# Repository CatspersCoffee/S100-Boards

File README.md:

# S100-Boards

S-100 bus boards designed, laid out and built for a home-built S-100 system between 2013 and 2016: Z80 and 80386 CPU cards, static and dynamic memory, I/O and SPI peripheral cards, an 18-slot backplane and bus termination. The designs are in KiCad, with Xilinx CPLD and FPGA logic on most boards.

## Background

The S-100 bus began with the MITS Altair 8800 in 1975 and was standardised as IEEE-696 in 1983. Hobbyists still design new boards for it today. John Monahan's S100Computers.com and the N8VEM project are two well-known sources, and several boards here started from their designs.

This work ran from 2013 to 2016:
- **2013:** a Z80 single-board computer and the 18-slot backplane.
- **2014:** the Z80 CPU card, the 8MB SRAM boards, the serial-flash development board and the Spartan-6 I/O card.
- **2015:** the CPLD versions of the Z80 card, the 80386 CPU card, the SPI I/O board and the 32-bit memory experiments.
- **2016:** a revised backplane and the 8259A/SPI board.

The original S-100 cards of the 1970s and 80s were built from dozens of TTL chips, and later from HCMOS. A thread running through these boards is to move that glue logic into Xilinx CPLDs (XC9572, XC9572XL, XC95288XL) and Spartan-6 FPGAs. This covers bus status decoding, board select and address compare, memory bank and chip-select decoding, and I/O port decoding.
- **8MB SRAM board:** Rev 1 uses 27 TTL logic chips. Rev 2 does the same job with 14, one of them an XC9572XL.
- **Z80 CPU card:** from REV 4.0 an XC9572 takes over the S-100 status and control logic.
- **Other boards:** the CPLD or FPGA implements I/O ports and SPI interfaces that would otherwise need extra discrete logic.

## Boards

| Board | Folder | What it is | Status |
|---|---|---|---|
| Z80 CPU | [`Z80-CPU/`](Z80-CPU/) | Z80 bus-master CPU card, four revisions (REV 1.0–5.0); XC9572 CPLD from REV 4.0 | Built (all revisions) |
| 80386 CPU (V3.1) | [`80386-CPU/`](80386-CPU/) | John Monahan's S100Computers 80386 CPU board with small changes | Built |
| 18-slot backplane | [`Backplane-18-Slot/`](Backplane-18-Slot/) | 18-slot motherboard with active termination, Rev 1.0 and Rev 2.0 | Built (both) |
| Serial Flash board | [`Flash-UART/`](Flash-UART/) | USB UART, TMA lines and four SPI flash chips loaded over USB (CH341A); XC95288XL CPLD | Built |
| S6LX9 FPGA & I/O | [`S6LX9-FPGA-IO/`](S6LX9-FPGA-IO/) | Spartan-6 XC6SLX9 I/O card with RTC and serial RAM/flash | Built |
| MCP Serial Peripheral I/O | [`XC9500-IO/`](XC9500-IO/) | XC9572 CPLD + 12× MCP23S08 SPI port expanders (96 I/O lines) | Built |
| PIC-SPI | [`PIC-SPI/`](PIC-SPI/) | 8259A interrupt controller, SPI RTC/port expanders, 8× SPI flash; XC95288XL CPLD | Built |
| 8MB SRAM | [`SRAM-8MB/`](SRAM-8MB/) | 16 × 512 KB SRAM card, Rev 1 (TTL) and Rev 2.0 (XC9572XL CPLD) | Built (both) |
| x86 Memory Adapter + 4Mbit module | [`x86-Memory-Adapter/`](x86-Memory-Adapter/) | 32-bit memory adapter card (XC9572XL) and a 128K × 32 SRAM mezzanine (XC9536XL) | Module built; adapter not built |
| 4GB DRAM | [`DRAM-4GB-Unfinished/`](DRAM-4GB-Unfinished/) | Spartan-6 XC6SLX45 + DDR3 DIMM mezzanine for the memory adapter | Unfinished |
| Bus terminator | [`Bus-Terminator/`](Bus-Terminator/) | Plug-in active S-100 bus terminator | Built |
| Z80 FPGA SBC | [`Z80-FPGA-SBC/`](Z80-FPGA-SBC/) | 2013 Z80 single-board computer with XC95288XL CPLD and XC6SLX9 FPGA | Not built |
| SX6-MEM | [`SX6-MEM/`](SX6-MEM/) | Spartan-6 + SDRAM DIMM daughterboard, schematic only | Unfinished |
| NOR-SRAM loader | [`NOR-SRAM-Loader/`](NOR-SRAM-Loader/) | XC9572XL CPLD design for a serial-NOR-to-SRAM loader board | CPLD only |

Each folder has its own README with the parts, how the board works, the files, and a short "Things to check" list where something in the files looks worth a second look.

## Board views

Front and back of each board, rendered from its fabrication gerbers (or from the PCB file where no gerbers were made).

### Z80 CPU: [`Z80-CPU/`](Z80-CPU/)
The Z80 bus-master CPU card (REV 5.0 shown), with an XC9572 CPLD for the S-100 status and control logic.

### 80386 CPU (V3.1): [`80386-CPU/`](80386-CPU/)
John Monahan's S100Computers.com 80386 CPU board, with small V3.1 changes (TO-220 5 V regulator in place of the TO-3 7805, SMD status LEDs, a power LED).

### 18-slot backplane: [`Backplane-18-Slot/`](Backplane-18-Slot/)
An 18-slot S-100 motherboard with on-board active termination and a reset circuit (Rev 2.0 shown).

### Serial Flash board: [`Flash-UART/`](Flash-UART/)
A USB serial port plus four SPI flash chips that a PC loads over USB and the S-100 side reads back into RAM, for quick development turnaround.

### S6LX9 FPGA & I/O: [`S6LX9-FPGA-IO/`](S6LX9-FPGA-IO/)
A general-purpose S-100 I/O card built around a Spartan-6 XC6SLX9, with a DS1302 RTC, serial RAM and SPI flash.

### MCP Serial Peripheral I/O: [`XC9500-IO/`](XC9500-IO/)
An XC9572 CPLD driving twelve MCP23S08 SPI port expanders for 96 I/O lines, plus two external SPI ports.

### PIC-SPI: [`PIC-SPI/`](PIC-SPI/)
An 8259A interrupt controller on the vectored-interrupt lines, with an XC95288XL CPLD running an SPI bus (RTC, port expanders) and eight SPI flash chips.

### 8MB SRAM: [`SRAM-8MB/`](SRAM-8MB/)
Sixteen 512 KB SRAMs as a 16-bit, 8 MB memory card; Rev 2.0 (shown) moves the TTL bus logic into an XC9572XL CPLD.

### x86 Memory Adapter and 4Mbit SRAM module: [`x86-Memory-Adapter/`](x86-Memory-Adapter/)
A 32-bit memory adapter card with an XC9572XL and 3.3 V buffers (top pair), and the 128K × 32 SRAM mezzanine that plugs onto it (bottom pair).

### 4GB DRAM (unfinished): [`DRAM-4GB-Unfinished/`](DRAM-4GB-Unfinished/)
A Spartan-6 XC6SLX45 and DDR3 DIMM mezzanine for the memory adapter; parts are placed but the DDR3 routing was never done.

### Bus terminator: [`Bus-Terminator/`](Bus-Terminator/)
A plug-in active terminator card that holds the S-100 lines at a regulated termination voltage, plus a reset circuit and two +5 V Molex power outlets.

### Z80 FPGA SBC: [`Z80-FPGA-SBC/`](Z80-FPGA-SBC/)
A 2013 Z80 single-board computer on an S-100 card with an XC95288XL CPLD, a Spartan-6 XC6SLX9, SRAM, a 16550 UART on USB and an 8255 (REV 2.0 layout shown).

### SX6-MEM: [`SX6-MEM/`](SX6-MEM/)
A schematic for a Spartan-6 XC6SLX25 and 168-pin SDRAM DIMM daughterboard. No PCB layout was made.

### NOR-SRAM loader: [`NOR-SRAM-Loader/`](NOR-SRAM-Loader/)
An XC9572XL CPLD design for a board that would copy a serial NOR flash into 1 MB of SRAM. Only the CPLD design exists.

## Tools
- KiCad 2013-07-07 (BZR 4022). The schematics use the legacy `.sch` format; newer KiCad versions need the symbol remap step when opening them.
- Xilinx ISE 14.7 for the CPLD and FPGA designs (schematic entry, `.ucf` pin maps, `.jed`/`.bit` programming files).

## History
The git history replays the original dated project backups, oldest first, with each commit dated from the files it contains (NZ time). Boards are interleaved by date. The last commit adds the READMEs, images and licenses.

Not included: tool output, KiCad backup and autorouter files, PDFs and datasheets, and third-party originals that were kept alongside the projects.

## Credits
Several boards started from other people's designs: John Monahan (S100Computers.com), Andrew Lynch and the N8VEM project, and Godbout/CompuPro. See [NOTICE](NOTICE) and each board's README.

## License
- Board and CPLD/FPGA designs: [CERN-OHL-S-2.0](LICENSES/CERN-OHL-S-2.0.txt).
- Documentation and images: [CC-BY-4.0](https://creativecommons.org/licenses/by/4.0/).

These cover the original work only; third-party parts keep their authors' rights (see [NOTICE](NOTICE)). Copyright text on fabricated boards ("ALL RIGHTS RESERVED") is left as built; these licenses apply to the files.

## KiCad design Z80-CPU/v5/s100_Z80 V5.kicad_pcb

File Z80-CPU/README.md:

# Z80 CPU

An S-100 bus-master CPU card built around a Zilog Z80, in four revisions (silkscreen REV 1.0 to REV 5.0), 2014–2016. From REV 4.0 on, most of the bus control logic is in a Xilinx XC9572 CPLD.

## Status
All four revisions were built: v2 (REV 1.0), v3 (REV 2.0), v4 (REV 4.0) and v5 (REV 5.0).
The v4 gerbers are in a folder named `SENT to PCBway 28-07-2015`.

## Revisions
| Folder | Silkscreen | Main change | Design dates |
|---|---|---|---|
| `v2/` | "Z80 CPU BOARD", REV 1.0 | First board, all TTL, 2732 ROM. Files keep the `s100_Z80 V2` name of the S100Computers "VERSION 02" design they started from | Jun 2014 (schematic notes to Aug 2015) |
| `v3/` | "Z80 CPU" logo, REV 2.0 | Re-layout, master oscillator and CLK DIVISION jumpers, pSYNC DIP switch | Jul–Aug 2014 |
| `v4/` | "Z80 CPU - REV 4.0 © 2015 A Burrows" | XC9572 PC84 CPLD (IC1) takes over the S-100 status/control logic, Xilinx JTAG header, CPLD I/O headers | Jun–Jul 2015 (schematic updated Dec 2015) |
| `v5/` | "Z80 CPU © 2015 A Burrows", REV 5.0 | 2764 ROM (2732 still fits), 74LVC573 latches instead of 74LS541 buffers, CPLD wired to the data bus, ROM LOCK and CLK SEL jumpers | Dec 2015–Jan 2016 (board edit Oct 2016) |

There is no REV 3.0.

Left: REV 4.0 (`v4/`). Right: REV 5.0 (`v5/`).

## Hardware (v5)
| Ref | Part | Role |
|---|---|---|
| U1 | Z80 (40-DIP) | CPU |
| IC1 | Xilinx XC9572, PC84 (PLCC socket) | Bus status/control, reset, wait and ROM-enable logic |
| U13 | 2764 EPROM (2732 also fits, silkscreen "2764/2732") | On-board ROM |
| U2, U3, U12, U22 | 74LVC573 | Address and status latches to the S-100 bus (v4: 74LS541 buffers) |
| U19, U20 | 74LS244 | Data bus buffers |
| U29, U30, U32, U39 | 74LS273 | Latches/ports |
| U21 | 74LS541 | Clock and control buffers to the bus |
| U9, U10, U11 | 74LS165 | Wait-state shift registers, loaded from DIP switches SW2–SW4 |
| U14 | 74LS682 | 8-bit comparator |
| P3 | DIL14 oscillator ("CLK_CPU", "OSC") | CPU clock source |
| U48 | 7805 LDO | 5 V regulator |

- **Board:** 254.0 x 134.6 mm (10.0 x 5.3 in), two layers, the same outline on all revisions.
- **Switches and jumpers (v5):** DIP switches "RAM WAIT", "I/O WAIT" and "ROM WAIT". SW1 "RESET". K1 "ROM LOCK". P6 "CLK SEL". P7 "NMI ENABLE". P5 "XILINX CABLE" (JTAG). P11 is the CPLD I/O header.
- **LEDs (v5):** "Z80 BUS MASTER", "ROM SELECT", "WAIT", "POWER", and D4–D7, D9, D10 driven from the CPLD.
- **Tools:** KiCad (pcbnew 2013-07-07 BZR 4022-stable) and Xilinx ISE 14.7.

## How it works
- The Z80 drives the S-100 bus as bus master. CPU control lines (M1\*, RD\*, WR\*, MREQ\*, IORQ\*, REFSH\*) go into the CPLD. The CPLD produces the S-100 status and control signals:

  | Signal | S-100 pin |
  |---|---|
  | sINP | 46 |
  | sOUT | 45 |
  | sMEMR | 47 |
  | MWRT | 68 |
  | sWO\* | 97 |
  | sINTA | 96 |
  | pSYNC | 76 |
  | pWR\* | 77 |

  Pin numbers are from the UCF comments. On v4, sINP leaves through U22 to pin 46 and sWO\* to pin 97.
- The CPLD handles reset: the RESET button and slave clear go in, and the Z80 RESET\* comes out on CPLD P17.
- Wait states come from three DIP switches through 74LS165 shift registers. The CPLD gates the wait signal (WAITen, pin 25 on v4).
- The on-board ROM is enabled through the CPLD. Its enable line is called RomEn (CPLD P37) and its address-range input RomAddr (P45).
- In the v4 pin map, four CPLD LEDs (D4–D7) sit on P39, P40, P41 and P81. Port D0/D1 bit 7 are inputs.
- v2 and v3 have no CPLD; the same functions are built from 74LS/74S gates.

## CPLD (`cpld/`)
Two Xilinx ISE projects for the XC9572 PC84. Both pin maps are for the v4 board:
- `cpld/Z80_Board_V4/`: the first design. Top schematic `IC1v1.sch`, PISO shift-register sub-sheet `test1.sch` (also referenced by the project as `V4board-t2/PISO.sch`), `pinmap.ucf`, `IC1v1.jed`. Speed grade -10, July 2015.
- `cpld/z80v42/`: the second design. Revisions `IC1v2.sch`, then `IC1v2_2` to `IC1v2_7.sch`. The project top is `IC1v2_7`, with `IC1v2pinmap.ucf` and `IC1v2_7.jed`. Speed grade -7, Aug–Dec 2015. The pin map header reads "PIN MAP OF IC1 on Z80 Board V4". It uses CPLD pins that the v4 schematic notes as wire modifications ("Modification: tied to CPLD P37", "tied to CPLD P45 …").

## Files
| Path | Contents |
|---|---|
| `v2/`, `v3/`, `v4/`, `v5/` | KiCad project per revision: `.sch` and `-cache.lib` (schematic with its symbols), `.kicad_pcb`, `.net`, `.cmp`, `.pro` |
| `v2/board.*` | v2 board files (the v2 PCB was named `board`) |
| `v2/`, `v4/` `*.csv`, `*.xlsx` | IC parts lists |
| `v*/GERBERS/` | Fabrication gerbers and drill file for each revision |
| `v5/logo/` | "Z80 CPU" logo bitmap and its KiCad footprint |
| `v2/Logisim circuits/1.circ` | Small Logisim sketch (A14, A15, IOREQ, S0, S1 decode) |
| `cpld/` | ISE schematics, pin maps, project files and final JEDEC files |

## History
The git history replays the original dated backups of all four revisions and the two CPLD projects, from June 2014 to October 2016.

## Things to check (TODO)
- **CPLD design for v5:** both CPLD projects target the v4 board with wire modifications. The v5 board connects IC1 differently in places. For example, P45 (RomAddr in the pin map) is on data bus D4, and P76 (Resbut in the pin map) goes to the U22 latch enable. A CPLD design for the v5 pinout is not in this folder.
- **v3 gerbers:** they are dated 2014-07-18. The v3 schematic and board were changed after that, up to 2014-08-09, so the gerbers don't match the final `v3/s100_Z80 V3.kicad_pcb`.
- **v5 board file vs gerbers:** `v5/s100_Z80 V5.kicad_pcb` was saved in Oct 2016, after the Jan 2016 gerbers. It has wider CLK_OSC traces and the bottom text "© 2016" (the gerbers say "© 2015").
- **v5 drill file:** `v5/GERBERS/s100_Z80 V5.drl` is about 21 hours older than the copper gerbers.
- **v4 drill file:** `v4/GERBERS/s100_Z80 V4.drl` is an RS-274X file exported from gerbv, not Excellon.

## Credits
- **Origin:** this board started from John Monahan's **S-100 Z80 CPU Board V2** ([S100Computers.com](http://www.s100computers.com)). Full credit to him for the original design.
  - The v2 files keep its `s100_Z80 V2` name, and the first v2 board file still carried its text "S-100 Z80 CPU BOARD VERSION 02".
  - All four schematics share component time stamps with the original.
  - The original files are not included here.
- **Libraries:** schematic symbols from the N8VEM KiCad libraries (`N8VEM-KiCAD`, `00N8VEM`; e.g. the S-100 edge connector), embedded in the `-cache.lib` files.

## License
Hardware: CERN-OHL-S-2.0 for the original work in this folder; see the repo NOTICE for third-party parts. Images and documentation: CC-BY-4.0.

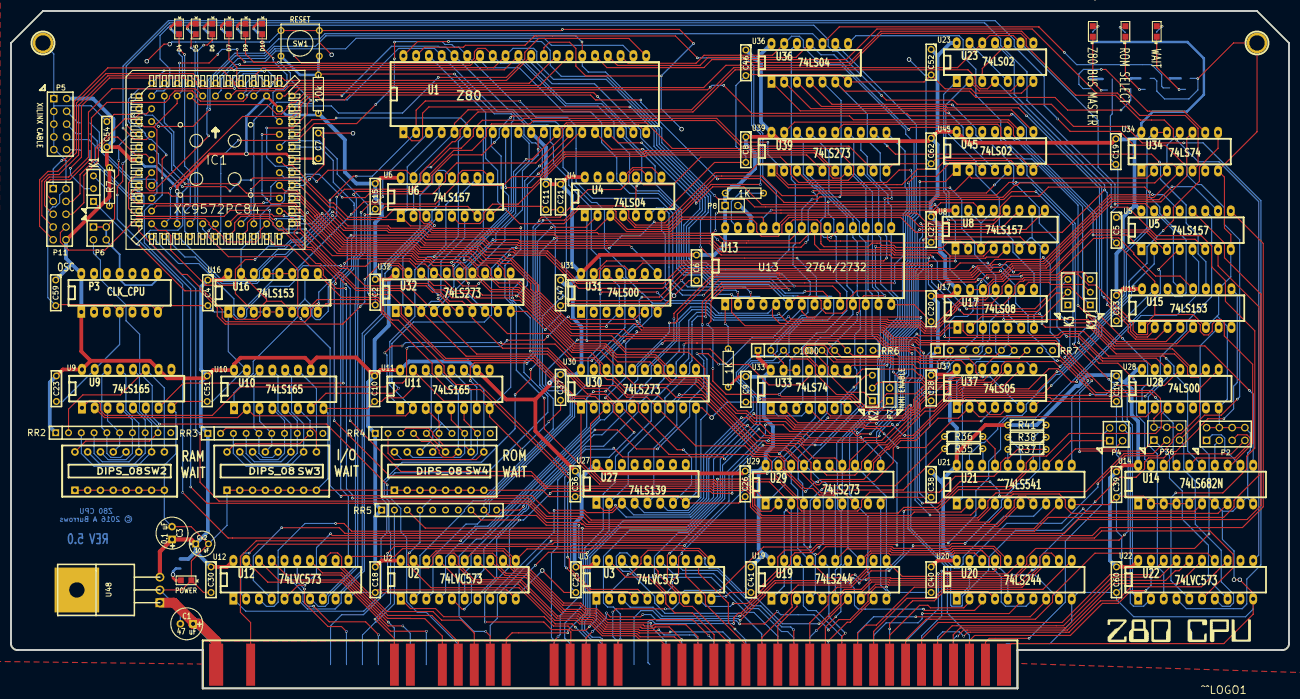
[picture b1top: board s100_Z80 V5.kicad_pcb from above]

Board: 2 copper layers, 254.0 x 134.6 mm, 139 parts (0 on the bottom side), 300 nets.

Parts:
C1: 47 uF; C1V7
C2, C4, C5, C6, C7, C8, C9, C10, C11, C13, C14, C15, C18, C19, C20, C23, C25, C26, C27, C28, C30, C36, C37, C38, C39, C40, C41, C46, C47, C51, C52, C54, C59, C60, C62: 0.1 uF; C2
C3: 0.1 uF; C1V7
C21: 100nF; C2
Cx2: 10 uF; C1V5
D1: ACTIVE; ^^LED-0805
D2: ROM; ^^LED-0805
D3: WAIT; ^^LED-0805
D4, D5, D6, D7, D9, D10: CP1; ^^LED-0805
D8: D2-1; ^^LED-0805
IC1: XC9572PC84; ^^XILINX-PLCC-S84
K1: ROM LOCK; SIL-3
K2: CONN_3; SIL-3
K3: SLAVE_CLR; SIL-3
K17: EN_WAITS; SIL-3
P1: S100_MALE
P2: CONN_4X2; pin_array_4x2
P3: CLK_CPU; DIP-14__300_ELL
P4: CONN_2X2; PIN_ARRAY_2X2
P5: XILINX CABLE2; PIN_ARRAY_5X2
P6: CLK SEL; PIN_ARRAY_2X2
P7: NMI; PIN_ARRAY_2X1
P8: CONN_2; PIN_ARRAY_2X1
P11: CONN_5X2; PIN_ARRAY_5X2
P34, P35: CONN_1; 1pin
P36: CONN_3X2; pin_array_3x2
Q1, Q2, Q3: ^^NPN-SOT23; ^^SOT-23
R1, R3, R4, R8, R13, R14, R15, R16, R17, R18: 330; ^^SMD_Resistor-0805
R2, R6, R9: 470; ^^SMD_Resistor-0805
R5, R20: 1K; R3
R7: 4K7; R3
R10, R11, R12: 100; ^^SMD_Resistor-0805
R19: 10k; R3
R35, R36, R37, R38: 10; R3
R41: 4700; R3
RR2, RR3, RR4, RR5, RR6: 1000; r_pack9
RR7: 4700; r_pack9
SW1: RESET; SW_PUSH_SMALL
SW2, SW3, SW4: DIPS_08; SWDIP8
U1: Z80; DIP-40__600_ELL
U2, U3, U12, U22: 74LVC573; DIP-20__300_ELL
U4: 74LS04; 14DIP-ELL300
U5, U6: 74LS157; 16DIP-ELL300
U8: 74LS157; DIP-16__300_ELL
U9, U10, U11: 74LS165; DIP-16__300_ELL
U13: 2764; DIP-28__600_ELL
U14: 74LS682N; DIP-20__300_ELL
U15: 74LS153; DIP-16__300_ELL
U16: 74LS153; 16DIP-ELL300
U17: 74LS08; DIP-14__300_ELL
U19, U20: 74LS244; DIP-20__300_ELL
U21: ^^74LS541; DIP-20__300_ELL
U23, U45: 74LS02; DIP-14__300_ELL
U26: ^^LOGO1; ***Z80cpuV32
U27: 74LS139; DIP-16__300_ELL
U28, U31: 74LS00; DIP-14__300_ELL
U29, U30, U32, U39: 74LS273; DIP-20__300_ELL
U33, U34: 74LS74; DIP-14__300_ELL
U36: 74LS04; DIP-14__300_ELL
U37: 74LS05; DIP-14__300_ELL
U48: LDO_REG_7805; ^^TO220

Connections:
/27_ROM_LOCK: K1.1, U32.19
/27_ROM_OE: IC1.37, U13.22, U28.10, U36.5
/+8V: C1.1, P1.1, P1.51, U48.1
/A0: P1.79, U2.12
/A1: P1.80, U2.13
/A2: P1.81, U2.14
/A3: P1.31, U2.15
/A4: P1.30, U2.16
/A5: P1.29, U2.17
/A6: P1.82, U2.18
/A7: P1.83, U2.19
/A8: P1.84, U3.12
/A9: P1.34, U3.13
/A10: P1.37, U3.14
/A11: P1.87, U3.15
/A12: P1.33, U3.16
/A13: P1.85, U3.17
/A14: P1.86, U3.18
/A15: P1.32, U3.19
/A16: P1.16, U12.12
/A17: P1.17, U12.13
/A18: P1.15, U12.14
/A19: P1.59, U12.15
/A20: P1.61, U12.16
/A21: P1.62, U12.17
/A22: P1.63, U12.18
/A23: P1.64, U12.19
/ADSB: U2.1, U3.1, U4.2, U12.1
/ADSB*: P1.22, RR5.9, U4.1, U37.4
/BUSAK*: U1.23, U36.13, U37.11
/BUSRQ*: U1.25, U34.5
/CDSB*: P1.19, RR6.7, U37.8, U37.13
/CLK_CPU: IC1.68, U1.6, U9.2, U10.2, U11.2, U33.11
/CLK_CPUneg: IC1.70, U33.3, U34.3, U34.11
/CLK_OSC: IC1.9, P3.8, P3.11, P6.1, P6.2, P6.4
/CLOCK*: P1.49, P4.2
/CPLD2_TCK: IC1.30, R10.1
/CPLD2_TDI: IC1.28, R11.1
/CPLD2_TDO: IC1.59, P5.8
/CPLD2_TMS: IC1.29, R12.1
/CPLD_CLKout1: IC1.10, U21.7
/CPLD_CLKout2: IC1.12, U21.6
/CPLD_P1: IC1.1, U1.22
/CPLD_P2: IC1.2, U1.34, U2.5, U13.6, U14.11
/CPLD_P3: IC1.3, P11.9
/CPLD_P4: IC1.4, P11.5
/CPLD_P5: IC1.5, K1.2
/CPLD_P6: IC1.6, U1.19
/CPLD_P7: IC1.7, U1.33, U2.6, U13.7, U14.8
/CPLD_P11: IC1.11, U1.28
/CPLD_P13: IC1.13, U22.4
/CPLD_P14: IC1.14, P36.1, U22.8
/CPLD_P15: IC1.15, P11.4
/CPLD_P17: IC1.17, RR7.4, U1.26, U17.3, U17.12, U17.13, U34.10
/CPLD_P18: IC1.18, U22.5
/CPLD_P19: IC1.19, P36.5, U22.7
/CPLD_P20: IC1.20, U22.6
/CPLD_P21: IC1.21, U1.4, U4.3, U6.1, U15.3, U23.11
/CPLD_P23: IC1.23, P11.6
/CPLD_P24: IC1.24, U1.8, U13.15, U19.11, U20.9, U29.13, U30.13, U32.13, U39.13
/CPLD_P25: IC1.25, R9.2, U36.10
/CPLD_P26: IC1.26, U1.5, U5.15, U6.15, U15.13, U23.9, U23.12
/CPLD_P31: IC1.31, U1.12, U13.13, U19.13, U20.7, U29.14, U30.14, U32.14, U39.14
/CPLD_P32: IC1.32, U1.15, U13.12, U19.15, U20.5, U29.17, U30.17, U32.17, U39.17
/CPLD_P33: IC1.33, U1.14, U13.11, U19.17, U20.3, U29.18, U30.18, U32.18, U39.18
/CPLD_P34: IC1.34, U1.2, U13.2, U16.3, U16.4, U16.5
/CPLD_P35: IC1.35, U1.3, U16.11, U16.12, U16.13
/CPLD_P36: IC1.36, U1.36, U2.3, U13.4, U14.15
/CPLD_P39: D4.1, IC1.39
/CPLD_P40: D5.1, IC1.40
/CPLD_P41: D6.1, IC1.41
/CPLD_P43: IC1.43, U1.35, U2.4, U13.5, U14.13
/CPLD_P44: IC1.44, U21.4
/CPLD_P45: IC1.45, U1.7, U13.16, U19.8, U20.12, U29.8, U30.8, U32.8, U39.8
/CPLD_P46: IC1.46, U21.3
/CPLD_P47: IC1.47, P36.3
/CPLD_P48: IC1.48, U22.3, U28.12
/CPLD_P50: D10.1, IC1.50
/CPLD_P51: IC1.51, U21.5
/CPLD_P52: IC1.52, P11.8
/CPLD_P53: IC1.53, U1.10, U13.18, U19.4, U20.16, U29.4, U30.4, U32.4, U39.4
/CPLD_P54: IC1.54, U8.1, U23.2, U23.6, U31.10
/CPLD_P55: IC1.55, U21.2
/CPLD_P56: IC1.56, U1.9, U13.17, U19.6, U20.14, U29.7, U30.7, U32.7, U39.7
/CPLD_P57: IC1.57, U1.13, U13.19, U19.2, U20.18, U29.3, U30.3, U32.3, U39.3
/CPLD_P58: IC1.58, U31.4, U31.9, U31.12
/CPLD_P61: IC1.61, U28.9
/CPLD_P62: D9.1, IC1.62
/CPLD_P63: IC1.63, U1.20
/CPLD_P65: IC1.65, U29.2
/CPLD_P66: IC1.66, U2.11, U3.11, U12.11
/CPLD_P67: IC1.67, U30.2
/CPLD_P69: IC1.69, U21.8
/CPLD_P71: IC1.71, U1.37, U2.2, U13.3, U14.17
/CPLD_P72: IC1.72, U1.21
/CPLD_P74: IC1.74, U28.1
/CPLD_P75: IC1.75, P11.1
/CPLD_P76: IC1.76, U22.11
/CPLD_P77: IC1.77, P11.7
/CPLD_P79: IC1.79, P11.3
/CPLD_P80: IC1.80, U1.30, U2.9, U13.10, U27.2
/CPLD_P81: D7.1, IC1.81
/CPLD_P82: IC1.82, U1.32, U2.7, U13.8, U14.6
/CPLD_P83: IC1.83, U1.31, U2.8, U13.9, U27.3
/CPLD_P84: IC1.84, U1.27
/DATA_OUT_ENABLE: U20.1, U20.19, U28.8
/DI0: P1.95, U20.17
/DI1: P1.94, U20.15
/DI2: P1.41, U20.13
/DI3: P1.42, U20.11
/DI4: P1.91, U20.8
/DI5: P1.92, U20.6
/DI6: P1.93, U20.4
/DI7: P1.43, U20.2
/DO0: P1.36, U19.3
/DO1: P1.35, U19.5
/DO2: P1.88, U19.7
/DO3: P1.89, U19.9
/DO4: P1.38, U19.12
/DO5: P1.39, U19.14
/DO6: P1.40, U19.16
/DO7: P1.90, U19.18
/DODSB*: P1.23, RR5.8, U28.2, U37.2
/ERROR*: P1.98, RR6.10
/HALT*: U1.18, U4.5
/HOLD*: P1.74, RR5.4, U34.2, U45.2
/INT*: P1.73, RR5.3, U21.9
/MWRT: P1.68, P4.4
/NDEF3: P1.66, P6.3
/NMI*: P7.1, RR6.4, U1.17
/NMI*s100: P1.12, U4.9
/PHI: P1.24, R41.2, U21.14
/PU1K-J: RR6.2, U33.12, U33.13, U36.12
/PU1K-JJ: P1.60, RR5.2
/PU1K-K: P1.26, RR6.3, U37.10
/PU1K-N: K2.1, RR6.5
/PU1K-R: K3.3, RR6.6
/PU1K-T: P1.18, RR6.8, U36.9, U37.6
/PU1K-Y: P1.58, RR6.9
/PU1K-waits: K17.3, RR5.10
/PU5K-A: RR7.2, U33.10
/PU5K-B: RR7.3, U34.1, U34.4
/PU5K-D: RR7.5, U33.1, U33.4
/PU5K-E: P1.3, RR7.6, U17.5
/PU5K-H: P1.72, RR7.7, U17.4
/PU5K-I: RR7.8, U21.1, U37.12
/RESET*: P1.75, R19.2, SW1.2, U17.1
/ROM_SELECT: R6.2, U31.13, U36.6
/WAIT*: U1.24, U17.8, U36.11
/Z80_ACTIVE: R2.2, U34.9
/bA8: U1.38, U8.14, U13.25
/bA9: U1.39, U8.11, U13.24
/bA10: U1.40, U8.5, U13.21
/bA11: U1.1, U8.2, U13.23
/bINT*: U1.16, U21.11
/pDBIN: P1.78, R35.1
/pSTVAL*: P1.25, R37.1
/pSYNC: P1.76, R36.1
/pWR*: P1.77, R38.1
/sHLTA: P1.48, U22.19
/sINP: P1.46, U22.17
/sINTA: P1.96, U22.13
/sM1: P1.44, U22.14
/sMEMR: P1.47, U22.16
/sOUT: P1.45, U22.18
/sWO*: P1.97, U22.15
GND: C1.2, C2.2, C3.2, C4.2, C5.2, C6.2, C7.2, C8.2, C9.2, C10.2, C11.2, C13.2, C14.2, C15.2, C18.2, C19.2, C20.2, C21.2, C23.2, C25.2, C26.2, C27.2, C28.2, C30.2, C36.2, C37.2, C38.2, C39.2, C40.2, C41.2, C46.2, C47.2, C51.2, C52.2, C54.2, C59.2, C60.2, C62.2, Cx2.2, D8.2, IC1.8, IC1.16, IC1.27, IC1.42, IC1.49, IC1.60, P1.50, P1.100, P2.2, P2.4, P2.6, P2.8, P3.4, P3.7, P5.1, P5.3, P5.5, P5.7, P5.9, P11.2, P34.1, P35.1, Q1.2, Q2.2, Q3.2, R13.1, R14.1, R15.1, R16.1, R17.1, R18.1, SW1.1, SW2.1, SW2.2, SW2.3, SW2.4, SW2.5, SW2.6, SW2.7, SW2.8, SW3.1, SW3.2, SW3.3, SW3.4, SW3.5, SW3.6, SW3.7, SW3.8, SW4.1, SW4.2, SW4.3, SW4.4, SW4.5, SW4.6, SW4.7, SW4.8, U1.29, U2.10, U3.10, U4.7, U5.8, U6.8, U8.3, U8.6, U8.8, U8.10, U8.13, U8.15, U9.8, U9.15, U10.8, U10.15, U11.8, U11.15, U12.10, U13.14, U13.20, U14.2, U14.3, U14.4, U14.5, U14.7, U14.9, U14.10, U15.1, U15.6, U15.8, U15.10, U15.15, U16.1, U16.6, U16.8, U16.10, U16.15, U17.7, U19.10, U20.10, U21.10, U22.10, U23.7, U27.8, U28.7, U29.10, U30.10, U31.7, U32.10, U33.7, U34.7, U36.7, U37.7, U39.10, U45.7, U48.2
unnamed: K1.3, R7.2
unnamed: U4.4, U23.8
unnamed: U5.6, U30.15
unnamed: U5.1, U39.19
unnamed: U5.3, U30.12
unnamed: U5.4, U12.2
unnamed: U5.5, U29.15
unnamed: U5.10, U30.19
unnamed: U5.11, U29.19
unnamed: U3.5, U16.7
unnamed: U3.6, U8.4
unnamed: U3.8, U8.9
unnamed: U6.14, U39.9
unnamed: U6.5, U39.5
unnamed: U3.3, U15.7
unnamed: U27.7, U32.11
unnamed: U5.12, U12.4
unnamed: P5.4, R12.2
unnamed: P5.6, R10.2
unnamed: P5.10, R11.2
unnamed: U5.13, U30.16
unnamed: U5.2, U29.12
unnamed: K17.1, U45.10
unnamed: U36.1, U45.4
unnamed: U27.5, U30.11
unnamed: U5.9, U12.5
unnamed: U5.7, U12.3
unnamed: U5.14, U29.16
unnamed: U27.4, U29.11
unnamed: U36.2, U45.8
unnamed: U15.11, U39.12
unnamed: U6.3, U32.2
unnamed: U6.4, U12.6
unnamed: U6.6, U32.5
unnamed: U6.9, U12.8
unnamed: U6.10, U32.6
unnamed: U6.12, U12.9
unnamed: U6.13, U32.9
unnamed: U23.3, U23.10
unnamed: U15.14, U16.14, U23.1
unnamed: U15.2, U16.2, U23.4
unnamed: U23.5, U23.13
unnamed: U3.4, U16.9
unnamed: U3.2, U15.9
unnamed: U6.11, U39.6
unnamed: U15.5, U39.15
unnamed: U6.2, U39.2
unnamed: U3.9, U8.12
unnamed: U3.7, U8.7
unnamed: U6.7, U12.7
unnamed: U15.12, U32.12
unnamed: U15.4, U32.15
unnamed: U27.6, U39.11
unnamed: U17.11, U29.1, U30.1, U32.1, U39.1
unnamed: U14.19, U36.3
unnamed: K3.2, U17.2
unnamed: U22.1, U36.8
unnamed: U4.6, U22.2
unnamed: R20.2, U13.1
unnamed: R5.2, U13.27
unnamed: P8.2, U13.26
unnamed: U17.6, U17.10
unnamed: K17.2, U17.9
unnamed: P7.2, U4.10
unnamed: U4.8, U4.11
unnamed: D4.2, R13.2
unnamed: D9.2, R17.2
unnamed: D7.2, R16.2
unnamed: D6.2, R15.2
unnamed: D5.2, R14.2
unnamed: U11.7, U45.5
unnamed: U10.7, U45.6
unnamed: D10.2, R18.2
unnamed: R37.2, U21.16
unnamed: R35.2, U21.18
unnamed: K2.3, U33.6
unnamed: K2.2, U34.12, U34.13
unnamed: U33.2, U45.1
unnamed: U33.8, U45.3
unnamed: P36.2, P36.4, P36.6, U31.5
unnamed: D1.1, R1.1
unnamed: D1.2, Q2.3
unnamed: Q2.1, R2.1
unnamed: D2.1, R3.1
unnamed: D2.2, Q3.3
unnamed: Q3.1, R6.1
unnamed: U10.1, U31.8
unnamed: RR3.5, SW3.12, U10.14
unnamed: RR3.8, SW3.15, U10.5
unnamed: RR3.9, SW3.16, U10.6
unnamed: RR3.6, SW3.13, U10.3
unnamed: RR3.7, SW3.14, U10.4
unnamed: RR4.7, SW4.14, U11.4
unnamed: RR4.6, SW4.13, U11.3
unnamed: RR4.8, SW4.15, U11.5
unnamed: RR4.5, SW4.12, U11.14
unnamed: RR4.9, SW4.16, U11.6
unnamed: U33.9, U37.1, U37.3, U37.5
unnamed: P4.1, U21.13
unnamed: P4.3, U21.12
unnamed: U33.5, U37.9
unnamed: RR2.5, SW2.12, U9.14
unnamed: RR2.9, SW2.16, U9.6
unnamed: RR2.6, SW2.13, U9.3
unnamed: RR2.7, SW2.14, U9.4
unnamed: RR2.8, SW2.15, U9.5
unnamed: U9.7, U45.9
unnamed: U9.1, U31.6
unnamed: U28.13, U36.4
unnamed: D3.1, R8.1
unnamed: D3.2, Q1.3
unnamed: Q1.1, R9.1
unnamed: D8.1, R4.1
unnamed: RR4.3, SW4.10, U11.12
unnamed: RR4.4, SW4.11, U11.13
unnamed: RR4.2, SW4.9, U11.11
unnamed: RR3.4, SW3.11, U10.13
unnamed: RR3.3, SW3.10, U10.12
unnamed: RR3.2, SW3.9, U10.11
unnamed: U11.1, U31.11
unnamed: U19.1, U19.19, U28.3
unnamed: P2.1, U14.12
unnamed: P2.3, U14.14
unnamed: P2.5, U14.16
unnamed: P2.7, U14.18
unnamed: U27.1, U28.11
unnamed: R36.2, U21.17
unnamed: R38.2, U21.15
unnamed: U21.19, U34.8
unnamed: RR2.3, SW2.10, U9.12
unnamed: RR2.4, SW2.11, U9.13
unnamed: RR2.2, SW2.9, U9.11
VCC: C2.1, C3.1, C4.1, C5.1, C6.1, C7.1, C8.1, C9.1, C10.1, C11.1, C13.1, C14.1, C15.1, C18.1, C19.1, C20.1, C21.1, C23.1, C25.1, C26.1, C27.1, C28.1, C30.1, C36.1, C37.1, C38.1, C39.1, C40.1, C41.1, C46.1, C47.1, C51.1, C52.1, C54.1, C59.1, C60.1, C62.1, Cx2.1, IC1.22, IC1.38, IC1.64, IC1.73, IC1.78, P3.1, P3.14, P5.2, P8.1, P11.10, R1.2, R3.2, R4.2, R5.1, R7.1, R8.2, R19.1, R20.1, R41.1, RR2.1, RR3.1, RR4.1, RR5.1, RR6.1, RR7.1, U1.11, U2.20, U3.20, U4.14, U5.16, U6.16, U8.16, U9.10, U9.16, U10.10, U10.16, U11.10, U11.16, U12.20, U13.28, U14.20, U15.16, U16.16, U17.14, U19.20, U20.20, U21.20, U22.20, U23.14, U27.16, U28.14, U29.20, U30.20, U31.14, U32.20, U33.14, U34.14, U36.14, U37.14, U39.20, U45.14, U48.3

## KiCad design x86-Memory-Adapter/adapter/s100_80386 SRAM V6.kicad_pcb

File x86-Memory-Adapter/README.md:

# x86 32bit Memory Adapter + 4Mbit SRAM module

Two boards from 2015–2016:
- **"x86 32bit Memory Adapter Board"**: an S-100-size card that connects the 80386 CPU board to a 32-bit, 3.3 V memory mezzanine.
- **"4Mbit (128K x 32)"**: an SRAM module for that mezzanine slot.

## Status
- **Adapter:** not built. Gerbers were plotted on 2015-04-25 (`adapter/GERBERS/`). The layout was changed after that (CPLD moved to the bottom side, LM2596 added, board re-routed up to 2016-01). No gerbers exist for the final layout.
- **SRAM module:** built. Gerbers were plotted on 2015-05-02 (`sram-module/GERBERS/`).

## Hardware

### Adapter (`adapter/`)
| Ref | Part | Role |
|---|---|---|
| U14 | XC9572XL-VQ44 | Control CPLD |
| U2–U6 | 74LVC573 | Latch the 80386 address (mA2–19, cA20–31) and byte enables mBE0–3* on `DB_ADS` |
| U10–U13 | 74LVX3245 | 32-bit data buffers, D0–31 (5 V) ↔ bD0–31 (3.3 V) |
| U9 | 74LVX3245 | Drives `DB_PHANTOM*` and `DB_WAIT` back up to 5 V for the 80386 board |
| U17, U8 | 74F04, 74F14 | Clock, `S100_SEL*` and `DB_ADS` conditioning |
| U1 | LM7805 | 5 V |
| U7 | LM1086 | 3.3 V |
| U20 | LT3081 | Adjustable rail |
| U19 | LM2596 | Buck pre-regulator (added 2015-07) |
| P5, P6 | 2×20, 2×25 headers | Ribbon connections to the 80386 CPU board (address/byte enables and data/control) |
| P8, P9 | 2×20 headers | 32-bit memory mezzanine slot |
| P11 | 2×2 header | JTAG to the mezzanine |
| P20 | S-100 edge | Power only (+8 V on pins 1/51, GND on pins 50/100) |

- **Size:** 254.00 × 134.62 mm, 2 layers.
- **Jumpers and headers** (silkscreen names):
  - **LT3081 Output Voltage Selector** (P13): 5.0 / 3.3 / 2.5 / 1.8 / 1.5 / 1.2 V.
  - **3.3V** (K1): takes 3.3 V from the LM1086 or the LT3081.
  - **5.0V** (K2): takes 5 V from the LM7805 or the LT3081.
  - **JTAG Chain** (P12): "2-4 CPLD only, 1-2 & 3-4 CPLD + FPGA". The second setting adds the mezzanine's device to the chain.
  - **XILINX CABLE** (P7, 2×7).
  - **CPLD Pins** (P10: CPLD pins 23 and 44).
  - JP5–JP7: tie S-100 pins 20, 53 and 70 to GND.
- **LEDs:**
  - POWER (D1);
  - `BOARD_SELECT` (D2, CPLD pin 32);
  - D5 and D6 (CPLD pins 33 and 31).

### SRAM module (`sram-module/`)
| Ref | Part | Role |
|---|---|---|
| U1–U4 | 128K×8 SRAM, SOP32 | One byte lane each: D0–7, D8–15, D16–23, D24–31 |
| U14 | XC9536XL-VQ44 | Byte-lane chip enables and write enables |
| U7 | LM1086 | 3.3 V from +8 V (P8 pins 1–4) |
| P8, P9 | 2×20 headers | Mezzanine connection to the adapter |
| P11 | 2×2 header | JTAG (TDO/TMS/TDI/TCK) |
| K1 | 3-pin header | CPLD pins 1, 34 and 36 (silkscreen "P1 / P34 / P36") |

- **Capacity:** 128K × 32 = **512 KB (4 Mbit)**, using word address lines A2–A18.
- **Slot headroom:** the P8/P9 slot also carries A19–A22 (unused on this module), which is enough for up to 8 MB.
- **Size:** 150.37 × 75.18 mm, 2 layers, 4 mounting holes.
- **LEDs:** POWER (D1), and D5/D6 (CPLD pins 33 and 31).

**KiCad (both boards):** 2013-07-07 BZR 4022 stable. The schematics are `EESchema Schematic File Version 2` and the PCBs are `kicad_pcb` version 3.

## How it works
- **No S-100 bus signals are used.** The adapter takes only power and GND from the S-100 edge connector. The 80386 CPU board drives the memory directly over the P5/P6 ribbon connectors.
- **Address and byte enables:** the five 74LVC573s latch the 80386 address and byte enables on `DB_ADS`.
  - A2–A22 go to the mezzanine as bA2–bA22.
  - The upper address bits (cA23–cA31) and the byte enables BE0–3* go both to the adapter CPLD and, over P9, to the mezzanine CPLD.
- **Data:** four 74LVX3245s buffer the 32-bit data bus between the 5 V 80386 side and the 3.3 V mezzanine.
  - Adapter CPLD pin 36 drives T/R (direction) on U10–U13.
  - CPLD pin 39 is on the same net as OE* of U10–U13.
- **Wait and phantom:** the adapter CPLD returns `DB_WAIT` and `DB_PHANTOM*` to the 80386 board through U9.
- **On the module:** the byte enables BE0–3* arrive on XC9536XL pins 14, 16, 18 and 19. The CPLD's pins 41–44 go to the four SRAM chip enables and pins 37–40 to the four write enables, one pair per SRAM.
  - The shared output enable of all four SRAMs is on module CPLD pin 12. It is also wired to P9 pin 26 (adapter CPLD pin 29).
  - Six further P9 pins link the two CPLDs directly (pins 2, 3, 5–8 on both).
- **JTAG chain:** P11 continues the adapter's chain into the module CPLD.
- **No CPLD source:** there is no CPLD project (no UCF or JEDEC) for either board in the original files.

## Files
| Path | Contents |
|---|---|
| `adapter/s100_80386 SRAM V6.*` | Adapter KiCad project (`.sch`, `-cache.lib`, `.pro`, `.kicad_pcb`, `.net`, `.cmp`) |
| `adapter/GERBERS/` | Adapter gerbers and drill file, plotted 2015-04-25 from the April layout |
| `sram-module/4Mem board v1.*` | Module KiCad project |
| `sram-module/GERBERS/` | Module gerbers and drill file, plotted 2015-05-02 |

Notes on the files:
- The adapter project keeps the file name of the Monahan design it started from (see Credits).
- The module gerbers of 2015-05-02 still contain a trial DDR3 DIMM footprint. The final module `.kicad_pcb` (2015-07-12) does not.
- The module schematic has an unannotated `SRAM_512KB` symbol placed outside the sheet. It is not in the netlist.

## History
The git history replays the original dated backups of both boards, from 2015-04-24 to 2016-01-13.

## Things to check (TODO)
- **Adapter:** U10–U13 OE* (net `CPLD_P39`) is driven by U17 (74F04) from `S100_SEL*` through one inverter, and it is also wired to CPLD pin 39. Check the polarity, and check that CPLD pin 39 is used only as an input.
- **Adapter:** the U6 (74LVC573) inputs D2–D7 (pins 4–9) are unconnected. So are the unused A/B pins of U9 (74LVX3245, pins 5–10 and 14–19). Check whether they need to be tied off.
- **Adapter:** U15 is a placeholder part, "ZZZZ1", in the final netlist and PCB. Check what it is meant to be.
- **Module:** the schematic note says "XC9532XL VQ44", but U14 is an XC9536XL-VQ44.

## Credits
- **The adapter started from John Monahan's S100 80386 SRAM V6 board** (S100Computers.com), the 32/64 MB SRAM board for his 80386 CPU board. Full credit to him for that design.
  - Evidence: the adapter's schematic keeps 49 of his component timestamps and his project file name.
  - The **P5/P6 interface to the 80386 board** keeps his pinout exactly.
  - The S-100 edge connector, card outline and card-ejector holes also come from his files.
- **New work in this folder:**
  - the CPLD and its logic connections;
  - the 3.3 V latches and buffers;
  - the power section (LM1086, LT3081, LM2596);
  - the JTAG chain;
  - the single 32-bit P8/P9 mezzanine pinout (his design used four byte-wide mezzanines);
  - the whole SRAM module.

## License
Hardware: CERN-OHL-S-2.0 for the original work in this folder. See the repo NOTICE for third-party parts.

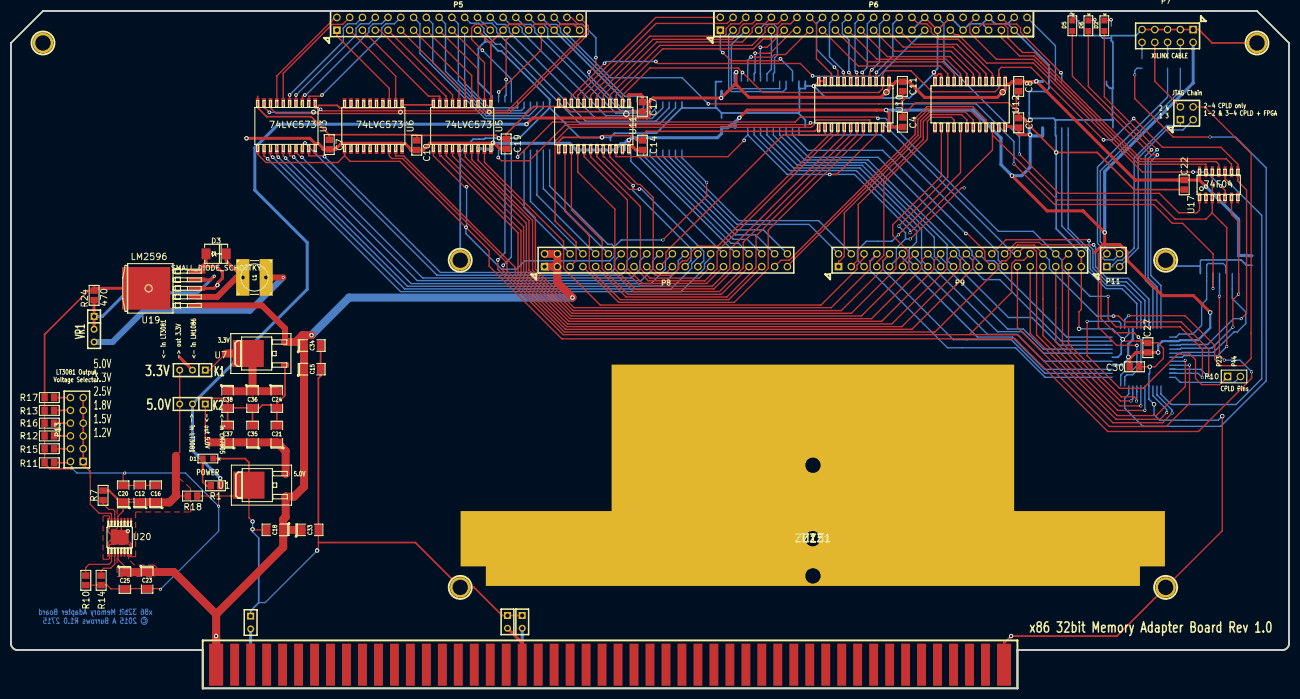
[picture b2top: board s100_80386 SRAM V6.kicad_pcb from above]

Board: 2 copper layers, 254.0 x 134.6 mm, 98 parts (0 on the bottom side), 199 nets.

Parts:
C1, C3, C4, C6, C7, C8, C9, C10, C11, C13, C14, C17, C19, C22, C26, C27, C28, C30, C32: 0.1 uF; ^^SMD_Resistor-0805
C12, C15, C16, C18, C20, C21, C23, C24, C25, C33, C34, C35, C36, C37, C38: 10 uF; SM1206_Opendous
D1: POWER; ^^LED-0805
D2, D5, D6: LED; ^^LED-0805
D3: SMALL_DIODE_SCHOTTKY; DO-214AA(SMB)
JP5, JP6, JP7: JUMPER; SIL-2
K1: 3.3V; SIL-3
K2: 5V; SIL-3
L1: SMALL_INDUCTANCE; Inductor_CDRH6D28
P1, P2, P3, P4, P34, P35: CONN_1; 1pin
P5, P8, P9: CONN_20X2; PIN_ARRAY_20X2
P6: CONN_25X2; PIN_ARRAY_30X2
P7: XILINX CABLE2; PIN_ARRAY_5X2
P10: CPLD Spare; PIN_ARRAY_2X1
P11: CONN_2X2; PIN_ARRAY_2X2
P12: JTAG CHAIN; PIN_ARRAY_2X2
P13: LT Output select; PIN_ARRAY_6X2
P20: S100_MALE
R1, R5, R6, R8: 330; ^^SMD_Resistor-0805
R2, R3, R4: 100; ^^SMD_Resistor-0805
R7: 4.53k; ^^SMD_Resistor-0805
R10: 500; ^^SMD_Resistor-0805
R11: 24.3K; ^^SMD_Resistor-0805
R12: 36.5K; ^^SMD_Resistor-0805
R13: 66.5K; ^^SMD_Resistor-0805
R14: 1K; ^^SMD_Resistor-0805
R15: 30.1K; ^^SMD_Resistor-0805
R16: 49.9K; ^^SMD_Resistor-0805
R17: 100K; ^^SMD_Resistor-0805
R18: 300; ^^SMD_Resistor-0805
R24: 470; ^^SMD_Resistor-0805
U1: LDO_REG_7805; ^^L7805C-TO252-2pin+tab
U2, U3, U4, U5, U6: 74LVC573; ^^SO-20wide
U7: LM1086CS_TO252_DPAK; -TO252
U8: 74F14; ^^SO14_wide
U9, U10, U11, U12, U13: 74LVX3245; ^^SO24W
U14: XC9572XL-VQ44; XILINX-VQ44
U15: ZZZZ1; ^^ZZZZZZ1
U17: 74F04; ^^SO14_wide
U19: LM2596; ^^TO263-51
U20: LT3081; ^^LT3081_TSSOP16
VR1: VR1; ^^Variable_Resistor

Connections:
/0V_A: JP5.2, P20.20
/0V_B: JP6.2, P20.53
/0V_C: JP7.2, P20.70
/+8Vi: C15.1, C18.1, C23.1, C25.1, C33.1, C34.1, P8.1, P8.2, P8.3, P8.4, P20.1, P20.51, U1.1, U7.2, U19.1, U20.12, U20.13, U20.14, U20.15
/BOARD_SELECT: D2.1, U14.32
/CLK: U14.1, U17.10
/CPLD1_TCK: P11.4, R2.1, U14.11
/CPLD1_TDI: R3.1, U14.9
/CPLD1_TDO: P12.4, U14.24
/CPLD1_TMS: P11.2, R4.1, U14.10
/CPLD_P2: P9.29, U14.2
/CPLD_P3: P9.31, U14.3
/CPLD_P5: P9.33, U14.5
/CPLD_P6: P9.35, U14.6
/CPLD_P7: P9.37, U14.7
/CPLD_P8: P9.38, U14.8
/CPLD_P12: P9.8, U5.18, U14.12
/CPLD_P13: P9.10, U5.17, U14.13
/CPLD_P14: P9.12, U5.16, U14.14
/CPLD_P16: P9.14, U5.15, U14.16
/CPLD_P18: P9.16, U5.14, U14.18
/CPLD_P19: P9.18, U5.13, U14.19
/CPLD_P20: P9.20, U5.12, U14.20
/CPLD_P21: P9.22, U6.19, U14.21
/CPLD_P22: P9.24, U6.18, U14.22
/CPLD_P23: P10.1, U14.23
/CPLD_P27: U9.21, U14.27
/CPLD_P28: U9.20, U14.28
/CPLD_P29: P9.26, U14.29
/CPLD_P30: P9.28, U14.30
/CPLD_P31: D6.1, U14.31
/CPLD_P33: D5.1, U14.33
/CPLD_P34: U8.3, U8.6, U14.34
/CPLD_P36: U10.2, U11.2, U12.2, U13.2, U14.36, U17.8
/CPLD_P37: U8.1, U14.37, U17.6
/CPLD_P38: U8.2, U14.38
/CPLD_P39: U10.22, U11.22, U12.22, U13.22, U14.39, U17.3, U17.12
/CPLD_P40: P9.30, U2.19, U14.40
/CPLD_P41: P9.32, U2.18, U14.41
/CPLD_P42: P9.34, U2.17, U14.42
/CPLD_P43: P9.36, U2.16, U14.43
/CPLD_P44: P10.2, U14.44
/D0: P6.30, U10.3
/D1: P6.28, U10.4
/D2: P6.26, U10.5
/D3: P6.24, U10.6
/D4: P6.22, U10.7
/D5: P6.20, U10.8
/D6: P6.18, U10.9
/D7: P6.16, U10.10
/D8: P6.14, U11.3
/D9: P6.12, U11.4
/D10: P6.10, U11.5
/D11: P6.8, U11.6
/D12: P6.6, U11.7
/D13: P6.4, U11.8
/D14: P6.2, U11.9
/D15: P6.33, U11.10
/D16: P6.32, U12.3
/D17: P6.29, U12.4
/D18: P6.27, U12.5
/D19: P6.25, U12.6
/D20: P6.23, U12.7
/D21: P6.21, U12.8
/D22: P6.19, U12.9
/D23: P6.17, U12.10
/D24: P6.15, U13.3
/D25: P6.13, U13.4
/D26: P6.11, U13.5
/D27: P6.9, U13.6
/D28: P6.7, U13.7
/D29: P6.5, U13.8
/D30: P6.3, U13.9
/D31: P6.1, U13.10
/DB_ADS: U2.11, U3.11, U4.11, U5.11, U6.11, U8.4
/DB_PHANTOM*: P6.50, U9.3
/DB_WAIT: P6.46, U9.4
/FPGA_TDI: P11.3, P12.3
/FPGA_TDO: P11.1, P12.1
/LM1086 out: C24.1, C36.1, C38.1, K1.1, U7.3
/LM2596output: L1.2, VR1.3
/LM7805 out: C21.1, C35.1, C37.1, K2.1, U1.3
/LTout: C12.1, C16.1, C20.1, K1.3, K2.3, R7.1, R18.1, U20.1, U20.2, U20.3, U20.4, U20.5, U20.8, U20.9, U20.16, U20.17
/S100_SEL*: P6.42, U17.13
/TDO_1: P7.8, P12.2
/V3.3: C1.1, C3.1, C4.1, C6.1, C7.1, C10.1, C13.1, C14.1, C19.1, C26.1, C27.1, C30.1, K1.2, P7.2, U2.20, U3.20, U4.20, U5.20, U6.20, U9.24, U10.24, U11.24, U12.24, U13.24, U14.15, U14.26, U14.35
/bA2: P8.6, U2.15
/bA3: P8.8, U2.14
/bA4: P8.10, U2.13
/bA5: P8.12, U2.12
/bA6: P8.14, U3.19
/bA7: P8.16, U3.18
/bA8: P8.18, U3.17
/bA9: P8.20, U3.16
/bA10: P8.22, U3.15
/bA11: P8.24, U3.14
/bA12: P8.26, U3.13
/bA13: P8.28, U3.12
/bA14: P8.30, U4.19
/bA15: P8.32, U4.18
/bA16: P8.34, U4.17
/bA17: P8.36, U4.16
/bA18: P8.38, U4.15
/bA19: P8.40, U4.14
/bA20: P9.2, U4.13
/bA21: P9.4, U4.12
/bA22: P9.6, U5.19
/bD0: P8.5, U10.21
/bD1: P8.7, U10.20
/bD2: P8.9, U10.19
/bD3: P8.11, U10.18
/bD4: P8.13, U10.17
/bD5: P8.15, U10.16
/bD6: P8.17, U10.15
/bD7: P8.19, U10.14
/bD8: P8.21, U11.21
/bD9: P8.23, U11.20
/bD10: P8.25, U11.19
/bD11: P8.27, U11.18
/bD12: P8.29, U11.17
/bD13: P8.31, U11.16
/bD14: P8.33, U11.15
/bD15: P8.35, U11.14
/bD16: P8.37, U12.21
/bD17: P8.39, U12.20
/bD18: P9.1, U12.19
/bD19: P9.3, U12.18
/bD20: P9.5, U12.17
/bD21: P9.7, U12.16
/bD22: P9.9, U12.15
/bD23: P9.11, U12.14
/bD24: P9.13, U13.21
/bD25: P9.15, U13.20
/bD26: P9.17, U13.19
/bD27: P9.19, U13.18
/bD28: P9.21, U13.17
/bD29: P9.23, U13.16
/bD30: P9.25, U13.15
/bD31: P9.27, U13.14
/cA20: P5.24, U4.8
/cA21: P5.22, U4.9
/cA22: P5.19, U5.2
/cA23: P5.17, U5.3
/cA24: P5.15, U5.4
/cA25: P5.13, U5.5
/cA26: P5.11, U5.6
/cA27: P5.9, U5.7
/cA28: P5.7, U5.8
/cA29: P5.5, U5.9
/cA30: P5.3, U6.2
/cA31: P5.1, U6.3
/mA2: P5.20, U2.6
/mA3: P5.18, U2.7
/mA4: P5.16, U2.8
/mA5: P5.14, U2.9
/mA6: P5.12, U3.2
/mA7: P5.10, U3.3
/mA8: P5.8, U3.4
/mA9: P5.6, U3.5
/mA10: P5.4, U3.6
/mA11: P5.2, U3.7
/mA12: P5.40, U3.8
/mA13: P5.38, U3.9
/mA14: P5.36, U4.2
/mA15: P5.34, U4.3
/mA16: P5.32, U4.4
/mA17: P5.30, U4.5
/mA18: P5.28, U4.6
/mA19: P5.26, U4.7
/mBE0*: P5.33, U2.2
/mBE1*: P5.29, U2.3
/mBE2*: P5.25, U2.4
/mBE3*: P5.21, U2.5
GND: C1.2, C3.2, C4.2, C6.2, C7.2, C8.2, C9.2, C10.2, C11.2, C12.2, C13.2, C14.2, C15.2, C16.2, C17.2, C18.2, C19.2, C20.2, C21.2, C22.2, C23.2, C24.2, C25.2, C26.2, C27.2, C28.2, C30.2, C32.2, C33.2, C34.2, C35.2, C36.2, C37.2, C38.2, D1.2, D3.1, JP5.1, JP6.1, JP7.1, P1.1, P2.1, P3.1, P4.1, P5.23, P5.27, P5.31, P5.35, P5.39, P6.31, P6.34, P6.35, P6.38, P6.39, P6.43, P6.44, P6.47, P6.48, P7.1, P7.3, P7.5, P7.7, P7.9, P9.39, P9.40, P20.50, P20.100, P34.1, P35.1, R5.1, R6.1, R8.1, R10.2, R11.2, R12.2, R13.2, R14.2, R15.2, R16.2, R17.2, R18.2, R24.2, U1.2, U2.1, U2.10, U3.1, U3.10, U4.1, U4.10, U5.1, U5.10, U6.1, U6.10, U7.1, U8.7, U9.2, U9.11, U9.12, U9.13, U9.22, U10.11, U10.12, U10.13, U11.11, U11.12, U11.13, U12.11, U12.12, U12.13, U13.11, U13.12, U13.13, U14.4, U14.17, U14.25, U19.3, U19.5, U19.6
unnamed: P7.6, R2.2
unnamed: P7.4, R4.2
unnamed: P7.10, R3.2
unnamed: D1.1, R1.2
unnamed: P13.2, R11.1
unnamed: R14.1, U20.11
unnamed: P13.4, R15.1
unnamed: P13.6, R12.1
unnamed: P13.8, R16.1
unnamed: P13.1, P13.3, P13.5, P13.7, P13.9, P13.11, U20.7
unnamed: P13.10, R13.1
unnamed: P13.12, R17.1
unnamed: R10.1, U20.10
unnamed: R7.2, U20.6
unnamed: D2.2, R8.2
unnamed: R24.1, U19.4, VR1.1, VR1.2
unnamed: D3.2, L1.1, U19.2
unnamed: D6.2, R5.2
unnamed: D5.2, R6.2
unnamed: P6.41, U17.9
unnamed: P5.37, U8.5
unnamed: P6.37, U17.5
unnamed: P6.36, U17.1
unnamed: P6.45, U17.11
VCC: C8.1, C9.1, C11.1, C17.1, C22.1, C28.1, C32.1, K2.2, R1.1, U8.14, U9.1, U10.1, U11.1, U12.1, U13.1, U17.14

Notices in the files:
Z80-CPU/v5/s100_Z80 V5.kicad_pcb:
© 2016 A Burrows
x86-Memory-Adapter/adapter/s100_80386 SRAM V6.kicad_pcb:
© 2015 A Burrows R1.0 2715
x86-Memory-Adapter/sram-module/4Mem board v1.kicad_pcb:
© 2015 A Burrows R1.0 1815
